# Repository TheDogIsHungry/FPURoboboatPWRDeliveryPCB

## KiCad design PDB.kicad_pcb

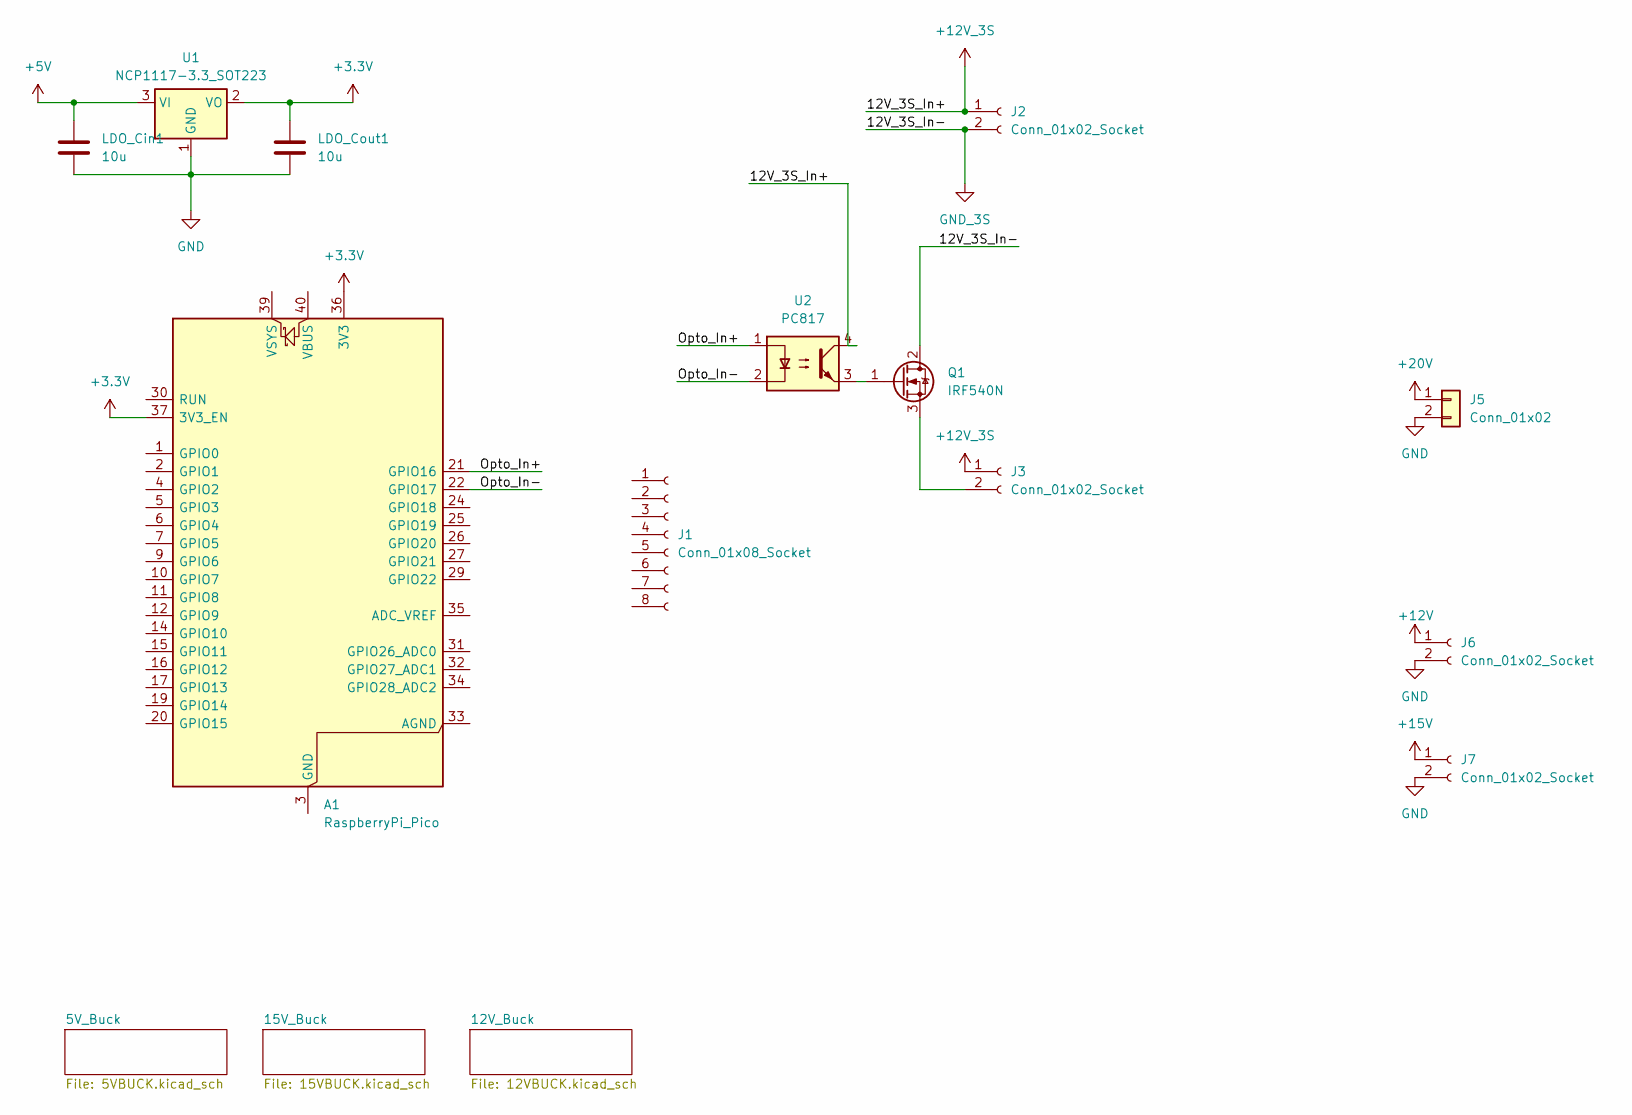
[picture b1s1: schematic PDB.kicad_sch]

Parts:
A1: RaspberryPi_Pico; RaspberryPi_Pico_Common_THT
J1: Conn_01x08_Socket; JST_XH_B8B-XH-AM_1x08_P2.50mm_Vertical
J2: Conn_01x02_Socket; AMASS_XT30U-M_1x02_P5.0mm_Vertical
J3, J6, J7: Conn_01x02_Socket; AMASS_XT30U-F_1x02_P5.0mm_Vertical
J5: Conn_01x02
LDO_Cin1: 10u; C_0805_2012Metric
LDO_Cout1: 10u; C_0805_2012Metric
Q1: IRF540N; TO-220-3_Vertical
U1: NCP1117-3.3_SOT223; SOT-223-3_TabPin2
U2: PC817; DIP-4_W7.62mm

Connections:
+3.3V: A1.36 (3V3), A1.37 (3V3_EN), LDO_Cout1.1, U1.2 (VO)
+5V: LDO_Cin1.1, U1.3 (VI); also elsewhere on the board
+12V: J6.1; also elsewhere on the board
+12V_3S: J2.1, J3.1, U2.4
+15V: J7.1; also elsewhere on the board
/Opto_In+: A1.21 (GPIO16), U2.1
/Opto_In-: A1.22 (GPIO17), U2.2
GND: J5.2, J6.2, J7.2, LDO_Cin1.2, LDO_Cout1.2, U1.1 (GND); also elsewhere on the board
GND_3S: J2.2, Q1.2 (D)
unnamed: A1.3 (GND), A1.8 (GND), A1.13 (GND), A1.18 (GND), A1.23 (GND), A1.28 (GND), A1.38 (GND)
unnamed: J3.2, Q1.3 (S)
unnamed: Q1.1 (G), U2.3

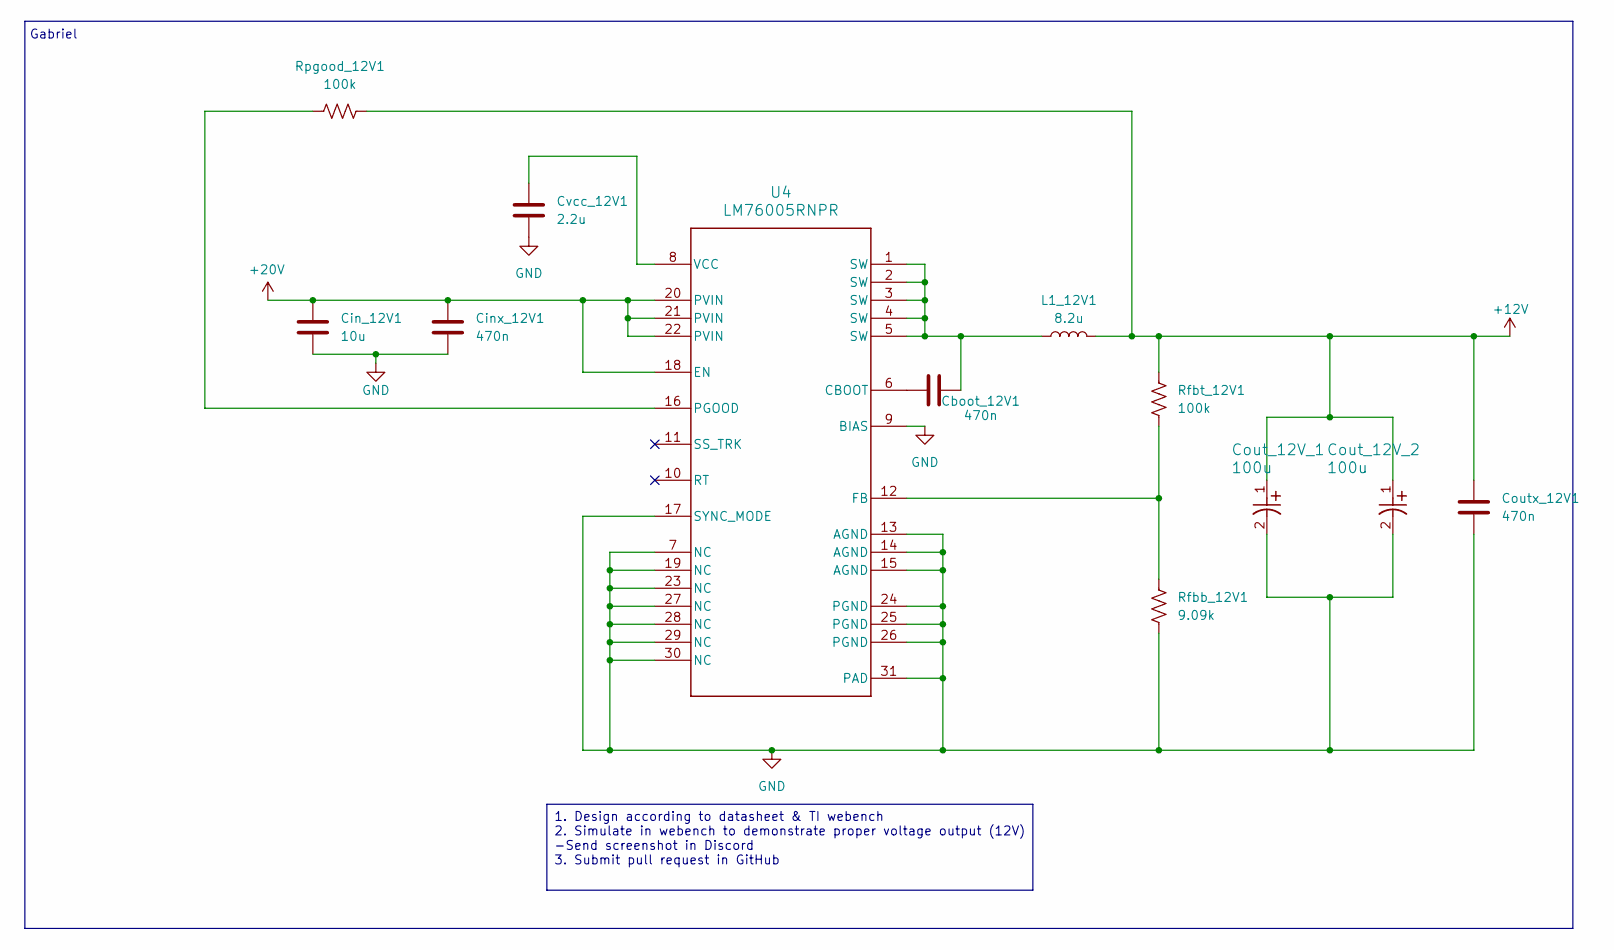
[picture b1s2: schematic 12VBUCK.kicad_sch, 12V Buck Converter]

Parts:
Cboot_12V1: 470n; C_0805_2012Metric
Cin_12V1: 10u; C_0805_2012Metric
Cinx_12V1: 470n; C_0805_2012Metric
Cout_12V_1, Cout_12V_2: 100u; CAP_EEFK_F_PAN
Coutx_12V1: 470n; C_0805_2012Metric
Cvcc_12V1: 2.2u; C_0603_1608Metric
L1_12V1: 8.2u; L_Bourns_SRP7028A_7.3x6.6mm
Rfbb_12V1: 9.09k; R_0603_1608Metric
Rfbt_12V1: 100k; R_0603_1608Metric
Rpgood_12V1: 100k; R_0603_1608Metric
U4: LM76005RNPR; RNP0030A

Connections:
+12V: Cout_12V_1.1, Cout_12V_2.1, Coutx_12V1.1, L1_12V1.2, Rfbt_12V1.2, Rpgood_12V1.2; also elsewhere on the board
+20V: Cin_12V1.1, Cinx_12V1.1, U4.18 (EN), U4.20 (PVIN), U4.21 (PVIN), U4.22 (PVIN); also elsewhere on the board
GND: Cin_12V1.2, Cinx_12V1.2, Cout_12V_1.2, Cout_12V_2.2, Coutx_12V1.2, Cvcc_12V1.2, Rfbb_12V1.1, U4.7 (NC), U4.9 (BIAS), U4.13 (AGND), U4.14 (AGND), U4.15 (AGND), U4.17 (SYNC_MODE), U4.19 (NC), U4.23 (NC), U4.24 (PGND), U4.25 (PGND), U4.26 (PGND), U4.27 (NC), U4.28 (NC), U4.29 (NC), U4.30 (NC), U4.31 (PAD); also elsewhere on the board
unnamed: Cboot_12V1.1, L1_12V1.1, U4.1 (SW), U4.2 (SW), U4.3 (SW), U4.4 (SW), U4.5 (SW)
unnamed: Cboot_12V1.2, U4.6 (CBOOT)
unnamed: Rfbb_12V1.2, Rfbt_12V1.1, U4.12 (FB)
unnamed: Rpgood_12V1.1, U4.16 (PGOOD)
unnamed: Cvcc_12V1.1, U4.8 (VCC)

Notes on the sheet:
Gabriel
1. Design according to datasheet & TI webench 2. Simulate in webench to demonstrate proper voltage output (12V) -Send screenshot in Discord 3. Submit pull request in GitHub

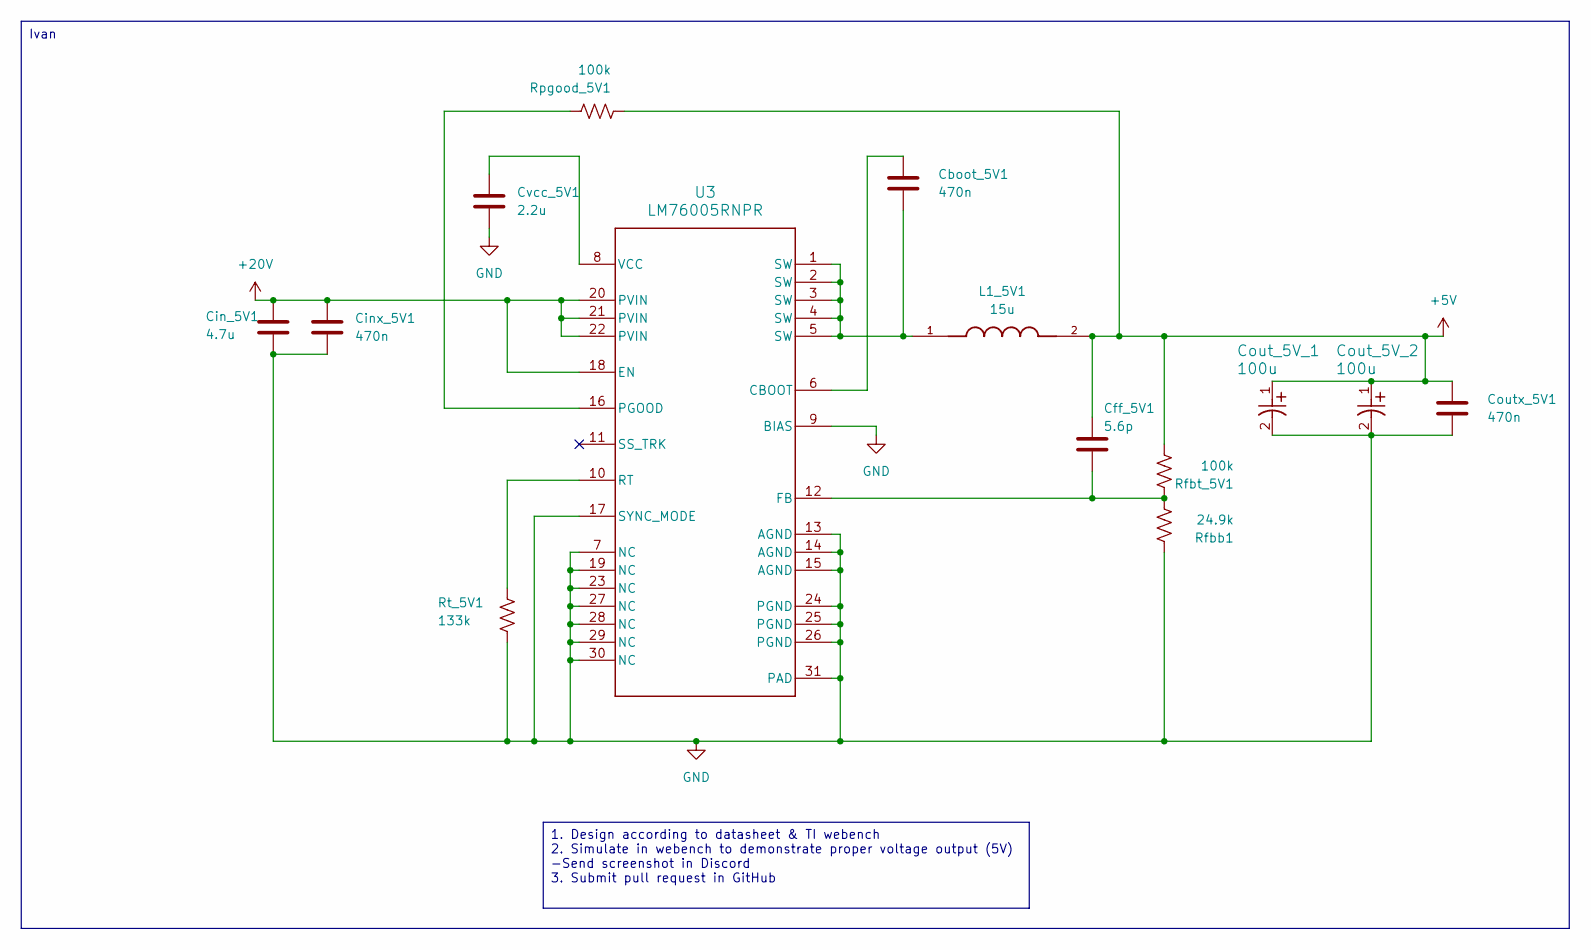
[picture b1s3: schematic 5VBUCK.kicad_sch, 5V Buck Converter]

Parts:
Cboot_5V1: 470n; C_0805_2012Metric
Cff_5V1: 5.6p; C_0603_1608Metric
Cin_5V1: 4.7u; C_0805_2012Metric
Cinx_5V1: 470n; C_0805_2012Metric
Cout_5V_1, Cout_5V_2: 100u; CAP_EEFK_F_PAN
Coutx_5V1: 470n; C_0805_2012Metric
Cvcc_5V1: 2.2u; C_0603_1608Metric
L1_5V1: 15u; IND_1217AS-H-150M=P3; PARTREV N/A
Rfbb1: 24.9k; R_0603_1608Metric
Rfbt_5V1: 100k; R_0603_1608Metric
Rpgood_5V1: 100k; R_0603_1608Metric
Rt_5V1: 133k; R_0603_1608Metric
U3: LM76005RNPR; RNP0030A

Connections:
+5V: Cff_5V1.1, Cout_5V_1.1, Cout_5V_2.1, Coutx_5V1.1, L1_5V1.2, Rfbt_5V1.2, Rpgood_5V1.2; also elsewhere on the board
+20V: Cin_5V1.1, Cinx_5V1.1, U3.18 (EN), U3.20 (PVIN), U3.21 (PVIN), U3.22 (PVIN); also elsewhere on the board
GND: Cin_5V1.2, Cinx_5V1.2, Cout_5V_1.2, Cout_5V_2.2, Coutx_5V1.2, Cvcc_5V1.2, Rfbb1.1, Rt_5V1.2, U3.7 (NC), U3.9 (BIAS), U3.13 (AGND), U3.14 (AGND), U3.15 (AGND), U3.17 (SYNC_MODE), U3.19 (NC), U3.23 (NC), U3.24 (PGND), U3.25 (PGND), U3.26 (PGND), U3.27 (NC), U3.28 (NC), U3.29 (NC), U3.30 (NC), U3.31 (PAD); also elsewhere on the board
unnamed: Cboot_5V1.2, L1_5V1.1, U3.1 (SW), U3.2 (SW), U3.3 (SW), U3.4 (SW), U3.5 (SW)
unnamed: Cboot_5V1.1, U3.6 (CBOOT)
unnamed: Cff_5V1.2, Rfbb1.2, Rfbt_5V1.1, U3.12 (FB)
unnamed: Rpgood_5V1.1, U3.16 (PGOOD)
unnamed: Rt_5V1.1, U3.10 (RT)
unnamed: Cvcc_5V1.1, U3.8 (VCC)

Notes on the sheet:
Ivan
1. Design according to datasheet & TI webench 2. Simulate in webench to demonstrate proper voltage output (5V) -Send screenshot in Discord 3. Submit pull request in GitHub

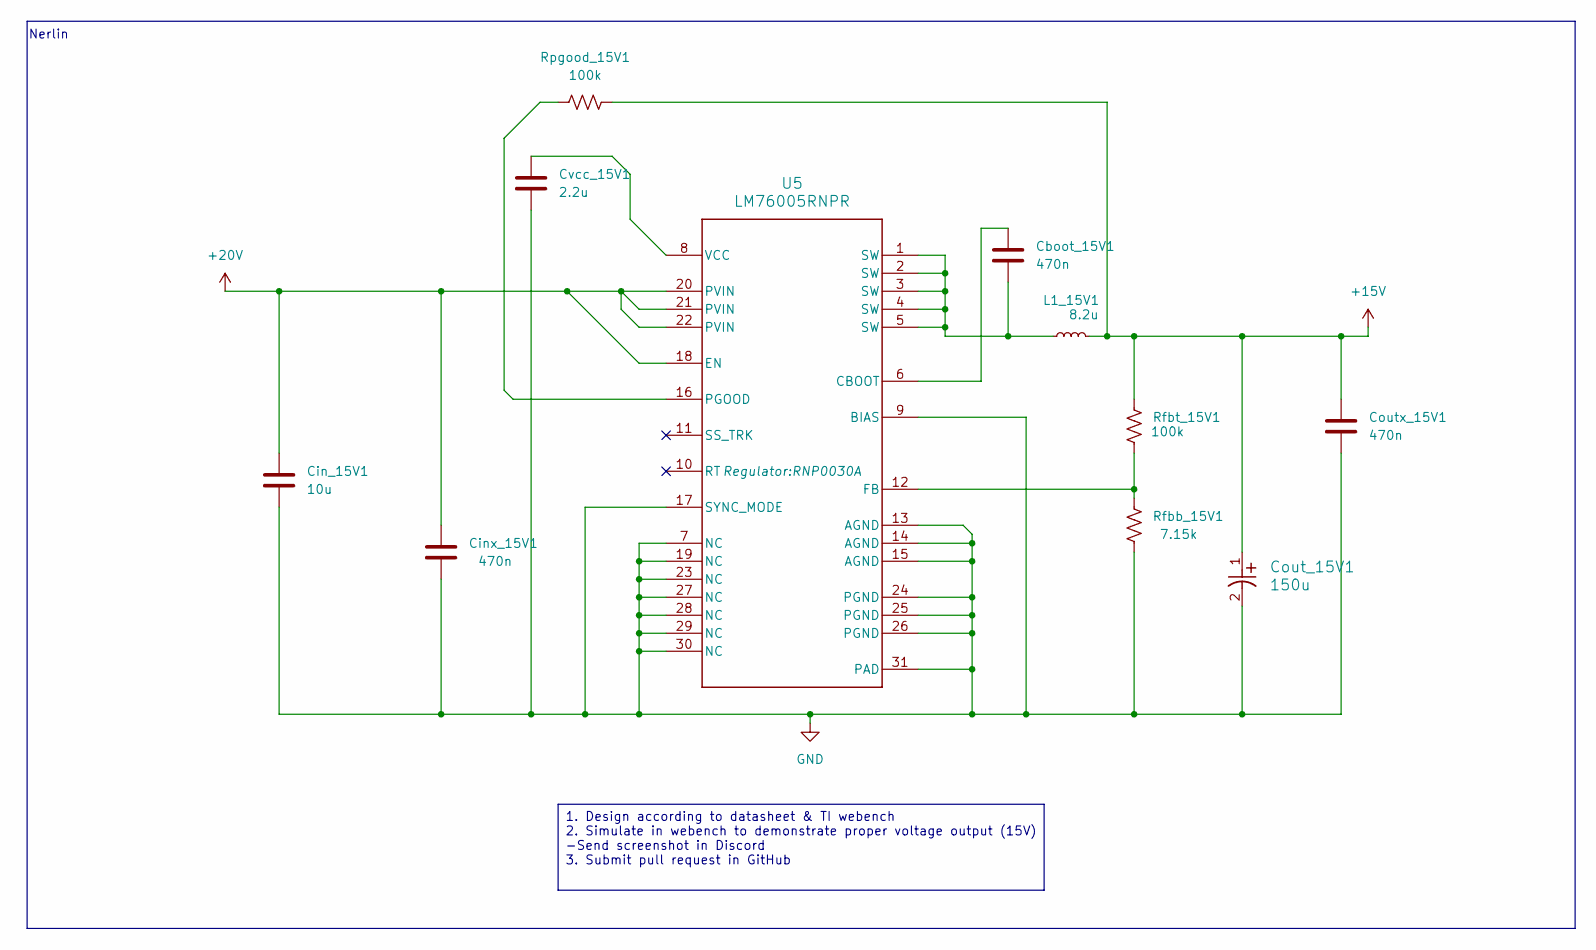
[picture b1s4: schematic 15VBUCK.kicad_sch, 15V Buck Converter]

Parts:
Cboot_15V1: 470n; C_0805_2012Metric
Cin_15V1: 10u; C_0805_2012Metric
Cinx_15V1: 470n; C_0805_2012Metric
Cout_15V1: 150u; CAP_EEFK_F_PAN
Coutx_15V1: 470n; C_0805_2012Metric
Cvcc_15V1: 2.2u; C_0603_1608Metric
L1_15V1: 8.2u; L_Bourns_SRP7028A_7.3x6.6mm
Rfbb_15V1: 7.15k; R_0603_1608Metric
Rfbt_15V1: 100k; R_0603_1608Metric
Rpgood_15V1: 100k; R_0603_1608Metric
U5: LM76005RNPR; RNP0030A

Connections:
+15V: Cout_15V1.1, Coutx_15V1.1, L1_15V1.2, Rfbt_15V1.2, Rpgood_15V1.2; also elsewhere on the board
+20V: Cin_15V1.1, Cinx_15V1.1, U5.18 (EN), U5.20 (PVIN), U5.21 (PVIN), U5.22 (PVIN); also elsewhere on the board
GND: Cin_15V1.2, Cinx_15V1.2, Cout_15V1.2, Coutx_15V1.2, Cvcc_15V1.2, Rfbb_15V1.1, U5.7 (NC), U5.9 (BIAS), U5.13 (AGND), U5.14 (AGND), U5.15 (AGND), U5.17 (SYNC_MODE), U5.19 (NC), U5.23 (NC), U5.24 (PGND), U5.25 (PGND), U5.26 (PGND), U5.27 (NC), U5.28 (NC), U5.29 (NC), U5.30 (NC), U5.31 (PAD); also elsewhere on the board
unnamed: Cboot_15V1.2, L1_15V1.1, U5.1 (SW), U5.2 (SW), U5.3 (SW), U5.4 (SW), U5.5 (SW)
unnamed: Cboot_15V1.1, U5.6 (CBOOT)
unnamed: Rfbb_15V1.2, Rfbt_15V1.1, U5.12 (FB)
unnamed: Rpgood_15V1.1, U5.16 (PGOOD)
unnamed: Cvcc_15V1.1, U5.8 (VCC)

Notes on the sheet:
Nerlin
1. Design according to datasheet & TI webench 2. Simulate in webench to demonstrate proper voltage output (15V) -Send screenshot in Discord 3. Submit pull request in GitHub

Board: 4 copper layers, 48 parts (0 on the bottom side), 29 nets, no tracks yet.
